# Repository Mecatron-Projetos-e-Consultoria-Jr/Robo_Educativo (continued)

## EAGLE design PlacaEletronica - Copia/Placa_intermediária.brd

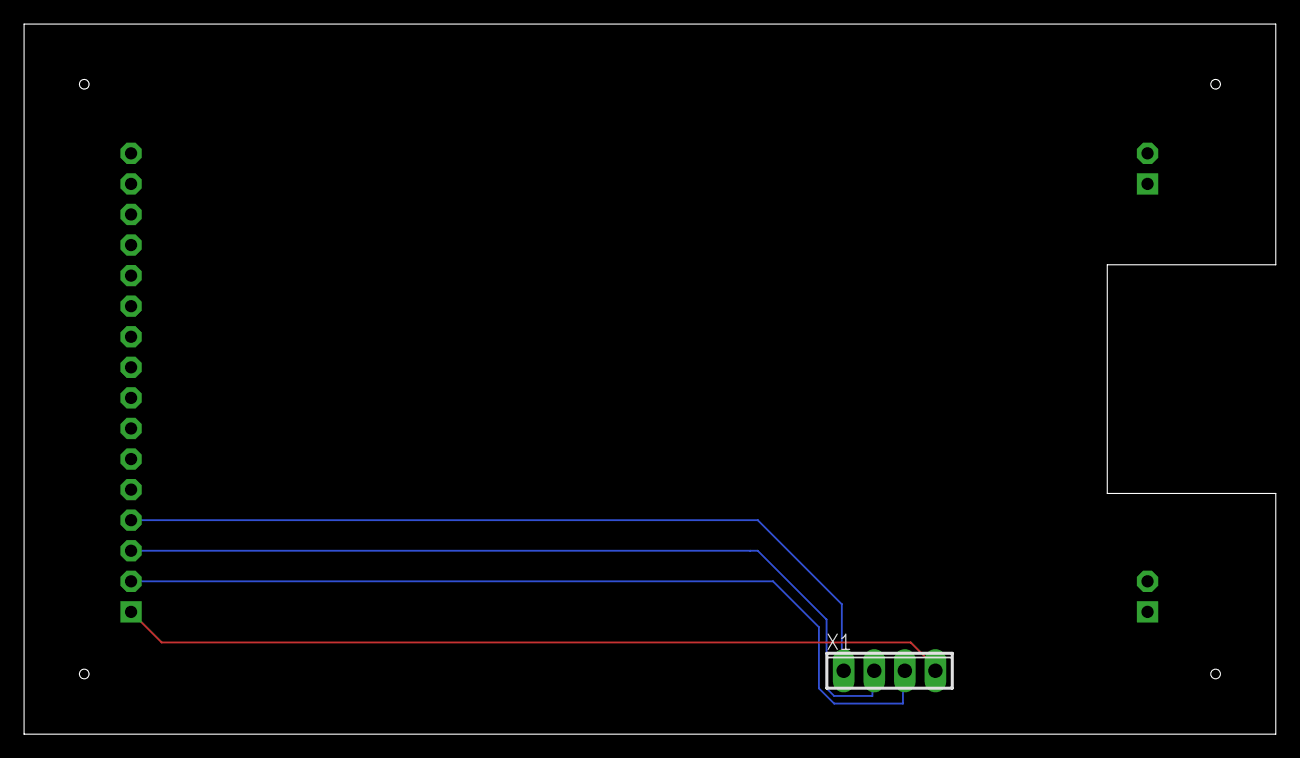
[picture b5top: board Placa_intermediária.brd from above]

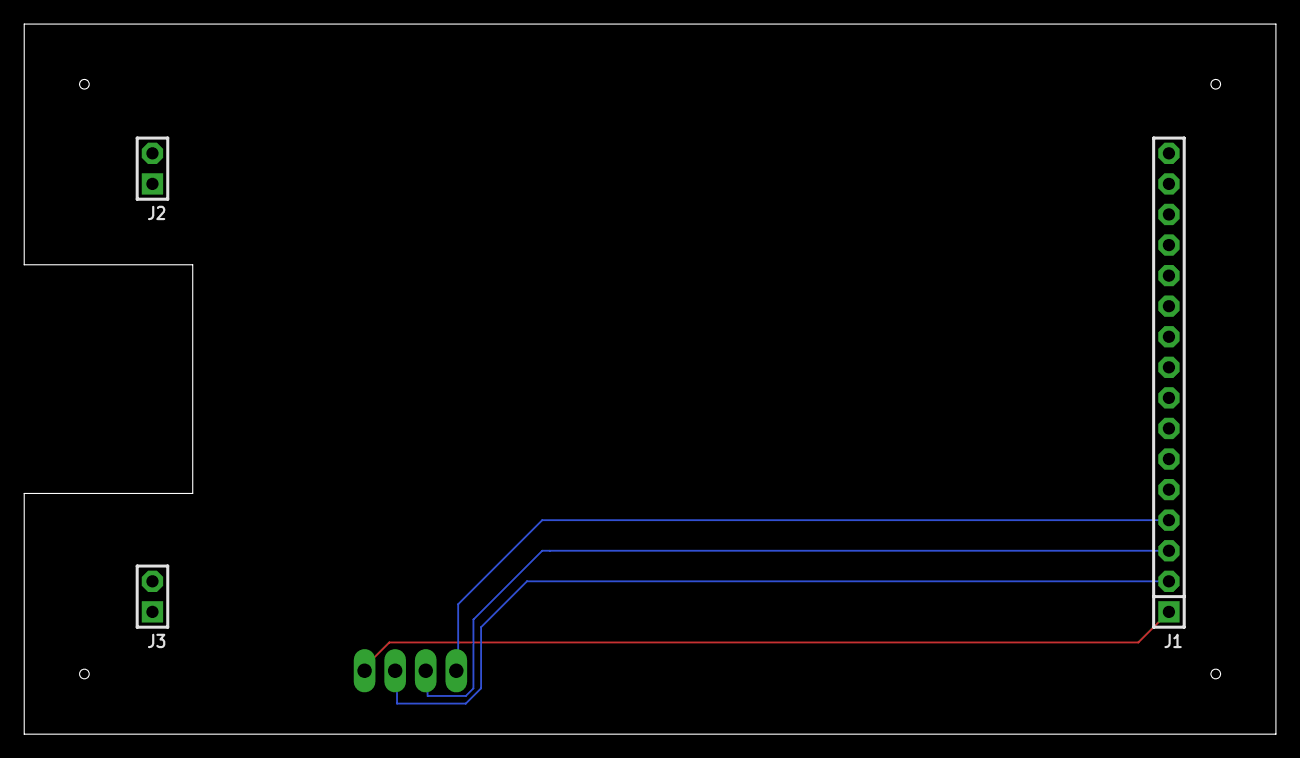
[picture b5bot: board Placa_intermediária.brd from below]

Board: 2 copper layers, 104.0 x 59.0 mm, 4 parts (3 on the bottom side), 4 nets.

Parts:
J1: F-1X16-SIP-100-40; SIP-100-16-40
J2, J3: F-1X02-SIP-100-40; SIP-100-02-40
X1: 4POL254

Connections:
5V: J1.4, X1.1
GND: J1.1, X1.4
SCREEN_RX: J1.2, X1.3
SCREEN_TX: J1.3, X1.2

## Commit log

2020-12-07 Adicionado biblioteca Nextion para ESP
2020-12-08 Adicionado pasta PlacaEletronica e Programacao
2020-12-09 PlacaPrincipal_AlteracoesResistoresCapacitoresPinhead
2020-12-11 BRDIncompleto_Compoentes_USB_Distantes
2020-12-11 BRDIncompleto Deletada backups automáticos do eagle
2020-12-15 Tudo funcionando perfeitamente antes de implementar upload OTA
2020-12-17 Implementacao Upload OTA
2021-01-25 Commit antes de migrar para o VSCode
2021-01-25 Prog arduino migrado para o VSCode [funcionando perfeitamente]
2021-01-26 Biblioteca Waveform
2021-01-26 Implementacao biblioteca waveform
2021-01-26 Implemenacao Biblioteca waveform[funcionando]
2021-01-27 Biblioteca Programação atual[completa - falta implementar]
2021-01-27 Biblioteca Programacao Manual implementada
2021-01-27 Painel Setting - Pegar o IP e SSID
2021-01-27 Programas pre gravados [estrutura]
2021-01-30 Primeiro programa feito
2021-01-30 Primeiro programama implementado
2021-01-31 Programas pre instalados - Estrutura está pronta
2021-02-09 Conversao da main para .ino
2021-02-09 Teste placa semáforo
2021-02-19 ProgMan Execução - Contagem regressiva
2021-02-24 Redesign IHM
2021-04-01 Criada a função next_init(), para evitar interferencia com o OTA
2021-04-10 Exemplos do grove, feito até o audio visualizer
2021-04-21 [MODIFIED] Troca de pinagem na placa principal
2021-04-22 [ADDED] 7 exemplos do Grove finalizados
2021-04-26 [MODIFIED] Borda superior da placa, posicao e sentido pin heads
2021-04-29 [Modified] Placa principal - Buzzer e conector alimentacao
2021-04-29 [MODIFIED] Organizacao das pastas em cada Chapter
2021-04-30 [MODIFIED] Queda de tensão analógicos, pino exclusivo GND_MOSFET
2021-05-13 [MODIFIED] Botoes Maiores e Troca do Regulador de Tensao
2021-05-14 [MODIFIED] Regulador de tensao em paralelo
2021-05-26 [MODIFIED] Mudado o divisor de tensão do FT
2021-06-02 [MODIFIED] Pinos do Engino
2021-06-08 [Added]Relatorios até o dia 08 de junho
2021-06-10 [MODIFIED]Nomeação dos Pinos do engino
2021-06-29 Relatorio 29 de junho
2021-07-22 [Modified] Placa principal - buzzer e alimentacao
2021-11-24 [ADDED] README Badge
